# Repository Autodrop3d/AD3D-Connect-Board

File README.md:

# AD3D-Connect-Board
Revision 1

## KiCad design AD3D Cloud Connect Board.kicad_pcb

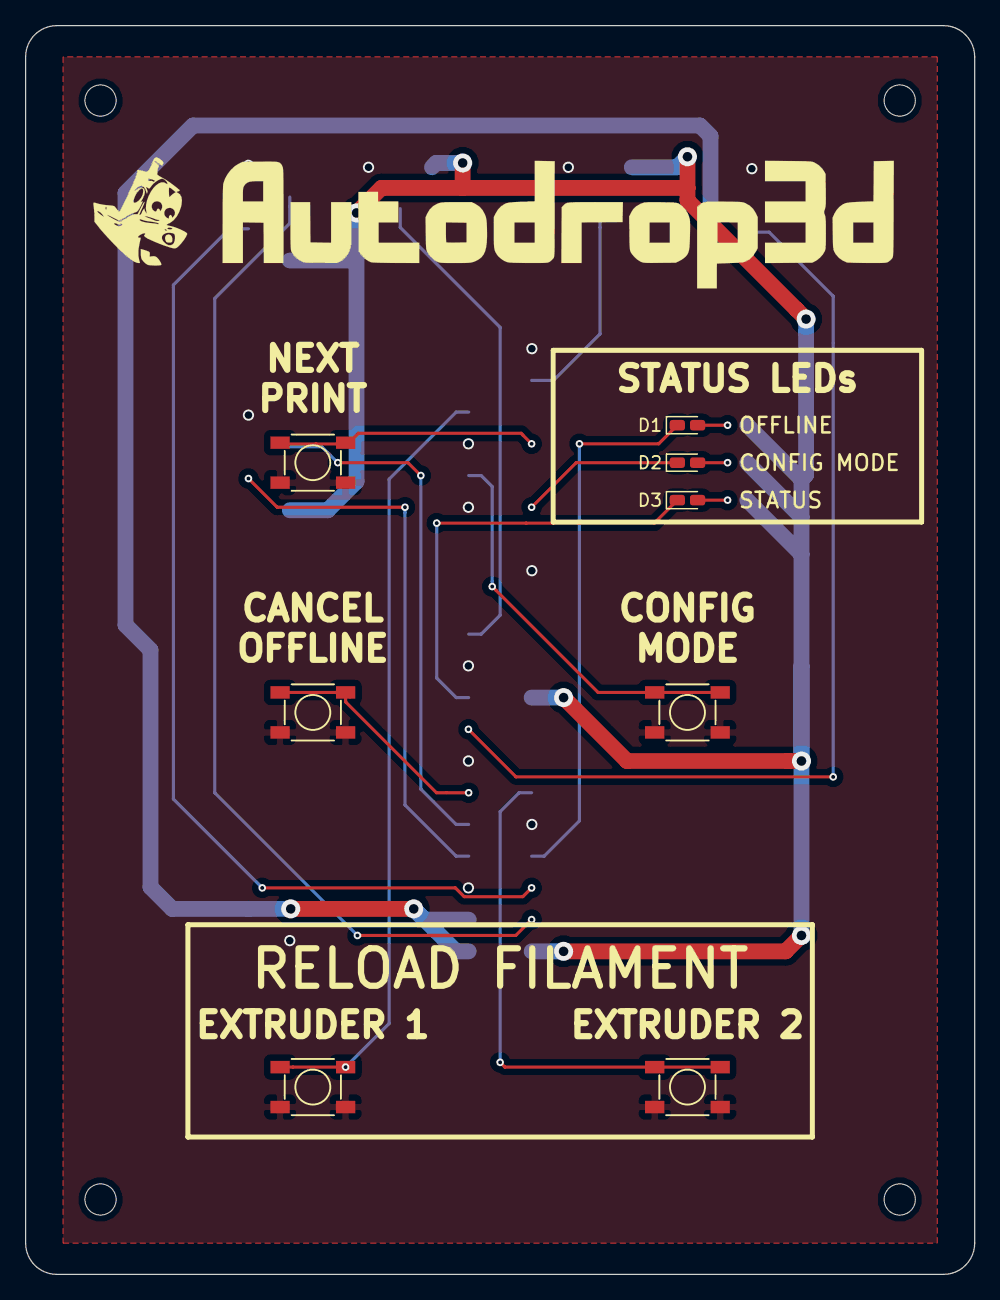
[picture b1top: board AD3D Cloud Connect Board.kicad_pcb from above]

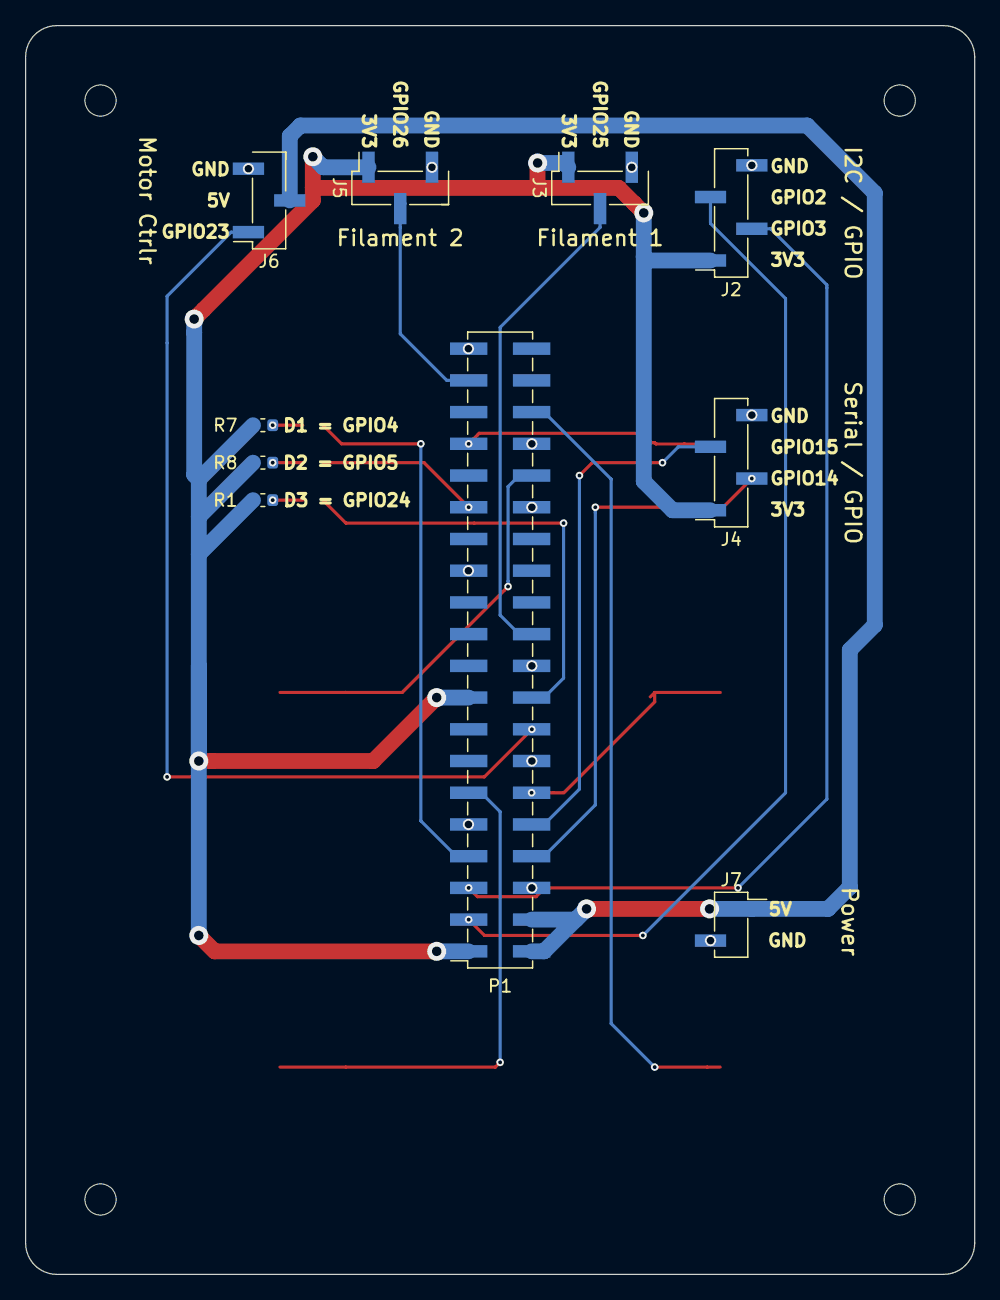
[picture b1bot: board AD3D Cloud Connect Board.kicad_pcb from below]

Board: 2 copper layers, 76.0 x 100.0 mm, 22 parts (10 on the bottom side), 21 nets.

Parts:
D1, D3: 150060RS75000; D_0603_1608Metric_Castellated
D2: 150060VS75000; D_0603_1608Metric_Castellated
J2, J4: Conn_01x04; PinHeader_1x04_P2.54mm_Vertical_SMD_Pin1Right
J3, J5, J6: Conn_01x03; PinHeader_1x03_P2.54mm_Vertical_SMD_Pin1Right
J7: Conn_01x02; PinHeader_1x02_P2.54mm_Vertical_SMD_Pin1Right
MK1, MK2, MK3, MK4: M2.5; MountingHole_2.5mm
P1: NPTC202KFMS-RC; PinSocket_2x20_P2.54mm_Vertical_SMD
R1, R7: 82 OHM 5%; R_0603_1608Metric
R8: 68 OHM 5%; R_0603_1608Metric
SW1: Config; SW_SPST_PTS647
SW2: Cancel/Offline; SW_SPST_PTS647
SW3: Next; SW_SPST_PTS647
SW4: Flmnt 1; SW_SPST_PTS647
SW5: Flmnt 2; SW_SPST_PTS647

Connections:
+3V3: J2.1, J3.1, J4.1, J5.1, P1.1, P1.17, R1.2, R7.2, R8.1
+5V: J6.2, J7.1, P1.2, P1.4
/GPIO2(SDA1): J2.3, P1.3
/GPIO3(SCL1): J2.2, P1.5
/GPIO4(GCLK): D1.1, P1.7
/GPIO5: D2.1, P1.29
/GPIO12(PWM0): P1.32, SW5.1, SW5.2
/GPIO13(PWM1): P1.33, SW3.1, SW3.2
/GPIO14(TXD0): J4.2, P1.8
/GPIO15(RXD0): J4.3, P1.10
/GPIO16: P1.36, SW1.1, SW1.2
/GPIO17(GEN0): P1.11, SW2.1, SW2.2
/GPIO18(GEN1)(PWM0): P1.12, SW4.1, SW4.2
/GPIO23(GEN4): J6.1, P1.16
/GPIO24(GEN5): D3.1, P1.18
/GPIO25(GEN6): J3.2, P1.22
/GPIO26: J5.2, P1.37
GND: J2.4, J3.3, J4.4, J5.3, J6.3, J7.2, P1.6, P1.9, P1.14, P1.20, P1.25, P1.30, P1.34, P1.39, SW1.3, SW1.4, SW2.3, SW2.4, SW3.3, SW3.4, SW4.3, SW4.4, SW5.3, SW5.4
unnamed: D1.2, R7.1
unnamed: D2.2, R8.2
unnamed: D3.2, R1.1

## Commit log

2019-09-21 Revision 1. Fixed button orientations split out LEDs Changed to standard 0.1" headers
2019-09-21 Forgot to update rev on sheets
